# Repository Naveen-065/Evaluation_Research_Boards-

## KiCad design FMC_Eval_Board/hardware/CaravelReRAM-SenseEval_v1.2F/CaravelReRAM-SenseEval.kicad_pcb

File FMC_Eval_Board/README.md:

# FMC Evaluation Board — SenseEval v1.2F / KC705

System snapshot dated **20 October 2026**. The active implementation is
[`output/kc705_cell_control`](output/kc705_cell_control). It adapts the evaluation
research board's scan-debug, Wishbone, and GUI logic to the SenseEval FMC PCB.

This folder contains all 20 saved FPGA bitstreams from the source workspace,
their available probes/checkpoints, controller and firmware sources, PCB design
files, simulations, measurements, test programs, and raw run records.
**Use the current image identified below for this assembled PCB.** Older images
are retained for traceability and include superseded pin-use, supply, diagnostic,
and startup configurations. They are not interchangeable with the current image.

## System and signal flow

```text
Browser at 127.0.0.1:8771
  -> local Python HTTP API
  -> SSH through Ubuntu VM
  -> Windows Vivado / JTAG
  -> KC705 FPGA, FMC J2
       -> Si5351A clock configuration via FMC management I2C
       -> DAC81416 SPI: supplies, biases, SET/RESET/read rails
       -> ADS5282 control and 10-MSPS LVDS acquisition
       -> Caravel scan control or Wishbone firmware command transport

Caravel supply/current path -> 56-ohm shunt -> preamplifier
  -> ADS5282 -> FPGA accumulation/trace -> GUI/API measurements

Ubuntu VM -> PCB FT232H -> Caravel housekeeping / SPI flash
```

The GUI follows the reference ScanDisk Monitor layout: cell map, operation
controls, API return log, and one logarithmic Read Trace with pulse-voltage bars.
Conductance shown in the GUI is an **estimate**, not a calibrated cell resistance.

## Contents

| Location | Purpose |
|---|---|
| `output/kc705_cell_control/build/` | Current `.bit`, matching `.ltx`, routed `.dcp`, timing/DRC and I/O audit |
| `output/kc705_cell_control/*.v`, `*.xdc` | Current RTL and exact electrical constraints |
| `output/kc705_cell_control/control.tcl`, `scan_ramp.tcl` | Runtime operations and bounded scan ramp |
| `output/kc705_cell_control/initialize.tcl` | Explicit FPGA, clock, DAC and ADC initialization |
| `output/kc705_cell_control/gui/` | Browser UI, API, SSH startup retry implementation |
| `output/kc705_cell_control/firmware/` | Caravel C source, binary, ELF, FT232H tools and firmware SDK |
| `output/kc705_cell_control/ip/` | Four Xilinx IP configurations retrieved from the build PC |
| `output/kc705_cell_control/tests/` | Model, GUI, RTL, ramp, protocol and transport tests |
| `output/kc705_cell_control/runs/` | Per-job parameters, decoded results, raw logs and traces |
| `output/kc705_cell_control/evidence/` | Deployment records, validation reports and screenshots |
| Other `output/` folders and `build_before_*`, `build_no_trace` | Historical bring-up, earlier images and diagnostic work |
| `hardware/` | Original schematic PDF/archive and editable KiCad board, schematic and libraries |
| `source_snapshot.json` | Source-to-copy inventory and original SHA-256 values |
| `package_state.json` | Bench/API state observed during packaging and dependency provenance |
| `SHA256SUMS`, `verify_package.py` | Final package integrity verification |

Historical readmes/logs describe the state when they were written. This README
describes the current controller; notably, scan SET/RESET now use ramps, WB holds
both SE and TM low, and the GUI has one reference-style Read Trace.

## Current deployment artifacts

All paths in this table are relative to `output/kc705_cell_control/`.

| Artifact | SHA-256 |
|---|---|
| `build/kc705_adc_capture.bit` | `fe31f0249b7081b4f6a00a721002317d618b0294cad9c5306f62853f5e34427c` |
| `build/kc705_adc_capture.ltx` | `6f800d28394e1f524304c3b59190f6ef819020bd2ff781928890fca4f9248e96` |
| `firmware/gui_wb_mode.bin` | `e7ad11e318b346edaae2fd0ff30736433fb27ef3bc5c39118ab4f1fc0a4107ef` |

FPGA: **XC7K325T-FFG900-2**, KC705. Build environment: Vivado **2026.1**.
The recorded image passed setup timing (+0.360 ns), hold timing (+0.059 ns),
and the critical DRC check. The 41 exported port-property records match the
audited baseline. Use the `.ltx` belonging to this `.bit`.

The FPGA image is loaded through JTAG into volatile configuration. A power cycle
requires checking/reinitializing the FPGA and peripheral state; this package
does not install an FPGA configuration-flash boot image.

## PCB wiring and fixed electrical settings

* **FMC VADJ is 1.8 V**, as measured on this KC705 after power cycling.
  Keep the supplied XDC pin mappings, I/O standards, drive, slew, pulls and
  termination unchanged. Runtime initialization does not issue VADJ/PMBus writes.
* FMC management I2C is a separate **3.3-V** bus at KC705 J2 **C30/C31**.
  It is not made 1.8 V by setting VADJ. The board was reworked by removing
  **R53, R54 and U18**, bridging **R53-2 to R58-2** and **R54-2 to R57-2**.
  Preserve this tested wiring; consult the schematic and rework evidence before
  using a differently assembled board.
* **NT22 connects DAC14 to VDDA1, target 3.0 V; NT12 is absent.**
  **DAC15 supplies VCCD2 at 1.8 V.** Runtime DAC commands cannot modify these
  protected supply channels or the reference/range configuration.
* R9, R10 and R11 are all **56 ohms** in the tested assembly. Earlier
  documents/simulations also contain previous shunt values.
* DAC internal-reference startup is included. U1 SDO is not connected:
  FPGA completion proves command transmission, not DAC register readback.
  Verify actual supply/bias voltages with a meter after assembly changes.
* ADC operation is 10 MSPS, offset binary, LSB first, with nominal internal
  94-ohm LVDS termination. Return clocks are checked at 10 MHz and 60 MHz.
* Caravel scan operation uses a 2-MHz Si5351 clock; WB uses 10 MHz.
  Each normal job restores scan read rails and holds Caravel CPU reset.

| ADC channel | Shunt / path | Preamplifier | Differential output pads |
|---|---|---|---|
| ADC1 | R9 / READ | U10 | R37 / R38 |
| ADC2 | R11 / RESET | U13 | R46 / R47 |
| ADC3 | R10 / SET | U11 | R39 / R40 |

Scan-debug cell reads principally use **DAC2/DAC3 and ADC3/R10** on this PCB.
Do not assume that the reference board's DAC channel numbers transfer directly.
Nominal preamplifier gain is 7; independent calibration remains pending.

Scan idle targets: DAC0=0.5 V, DAC1=2.5 V, DAC2=0.5 V, DAC3=2.5 V,
DAC5=2.3 V; DAC9/IREF=0.9 V, DAC10/VCOMP=0.9 V,
DAC11/BIAS_COMP2=0.6 V, DAC12/VBIAS=1.6 V, DAC13/DC_BIAS=1.0 V.
DAC4/6/7/8 are off (mask `0x01D0`).

WB uses DAC3 off, DAC4=0.5 V, DAC5=2.5 V, IREF=1.0 V and DC_BIAS=1.5 V;
other listed biases stay unchanged. Its power mask is `0x01CC`, disabling
physical DAC2/VCC_SET. Both SE and TM are actively low in WB; floating TXS0108E
inputs can otherwise select the wrong mode. Reset remains open-drain.

## Modes and ramp behavior

Scan GUI/API modes: `read`, `set`, `reset`, `cycle`, `column` (32 rows at one
column), and `array` (32 × 32). WB modes: `wb_read`, `wb_set`, `wb_reset`,
and `wb_cycle`. Do not infer additional WB array/column support from old scripts.
The approved programming test cells were **scan r0/c0** and **WB r0/c31**.

Scan SET/RESET use the reference ramp/read/confirm logic, with these PCB limits:

| Setting | SET | RESET |
|---|---|---|
| VCC sweep | 2.3, 2.4, 2.5 V | 2.3, 2.7, 3.0 V |
| WL sweep | 32 steps, 0.44–2.37 V | 32 steps, 0.94–2.88 V |
| Confirmation threshold | Current ≥35 µA | Current ≤5 µA |
| Consecutive confirmation reads | 10 | 10 |

GUI voltage fields are sweep ceilings. **Neither ramp may exceed 3.0 V.**
The DAC encoder also caps the output code at 39321 (ideal 2.999954 V), avoiding
rounding above the cap. This is a command limit, not an independent measurement
of analog overshoot or DAC accuracy.

Each step reads first, skips programming if the target is already confirmed,
otherwise applies one pulse, restores read rails (VCC=0.5 V, WL=2.5 V), reads
again, and confirms any threshold crossing. Default pulse length is 1.2 ms
(`hold=2400` at the 2-MHz scan clock). Invalid/clipped ADC feedback or Stop
terminates the sequence. Exhausting RESET without meeting its target stops
further requested cycles; completion does not imply a successful resistance change.

WB uses the Caravel firmware's native transaction sequence, including the
repeated program-packet workaround without an intervening reset. It does not
use the scan ADC-feedback ramp. Fifteen tagged/checksummed UART frames and
command echo are checked; raw TDC results remain uncalibrated.

## Running the system

The copied configuration records these existing bench addresses and paths:

| Component | Existing configuration |
|---|---|
| GUI host | This Windows PC; loopback port 8771 |
| Ubuntu VM / SSH jump | `ubuntu-24-04@100.98.132.51` |
| FPGA Windows PC through VM | `fpga@10.0.2.2`, host-key alias `100.86.99.88` |
| Remote controller folder | `C:/Users/fpga.DESKTOP-CVDV1JP/kc705_cell_control` |
| Vivado executable | `C:/AMDDesignTools2/2026.1/Vivado/bin/vivado.bat` |
| JTAG target | `localhost:3121/xilinx_tcf/Xilinx/00001f14c98801` |

Existing SSH keys/known-host identities are required; credentials are not part
of the package. Configure a different bench in `gui/server.py`, `bench.py` and
`i2c_host.tcl`. Merely copying this folder does not redeploy remote Tcl files.

1. Verify board wiring, power and the stated rails. Connect JTAG to the FPGA
   Windows PC and pass the PCB FT232H through to Ubuntu when flashing is needed.
2. Copy the current controller folder, including `build/`, `control.tcl`,
   `scan_ramp.tcl`, other Tcl helpers, and `evidence/`, to the configured remote
   controller directory. Do not deploy a historical sibling directory.
3. After power-up or when explicit reinitialization is needed, from the current
   controller directory run `python bench.py initialize`. This programs the
   FPGA, initializes Si5351/DAC/ADC, checks clocks, and leaves the CPU held.
   It does not flash Caravel firmware.
4. If Caravel firmware is missing, use Ubuntu's existing `caravel_venv` with
   PyFTDI/PyUSB, the packaged `firmware/` files and
   `python caravel_vm.py --flash gui_wb_mode.bin --hold-after`.
   Run this on Ubuntu with the PCB FT232H attached, while the bench is idle.
5. Start one GUI server from `output/kc705_cell_control`:

   ```powershell
   python gui/server.py --port 8771
   ```

   Open `http://127.0.0.1:8771/`, use **Check bench**, then a single **Read**.
   Dry run previews a request without hardware access; clear it to execute.
   Use Stop for a controlled abort and wait for the cleanup result.

Do not run two controller servers against the same hardware. The existing
server may still be running from the original workspace; close it before
starting the packaged copy. Export links provide averaged results and the
latest decimated raw trace.

## API, trace interpretation and SSH fix status

`POST /api/run` accepts the mode, row, col, four voltage ceilings, hold, cycles
and dry_run. `GET /api/status` reports current job and recorded measurements.
`POST /api/cancel {}` requests cleanup. CSV endpoints are `/api/export.csv`
and `/api/trace.csv`; the new backend also exposes `/api/run-log/<job-id>`.

Example scan ramp cycle, which changes cell state if `dry_run` is false:

```json
{"mode":"cycle","row":0,"col":0,"set_v":2.5,"set_wl":2.37,
 "reset_v":3.0,"reset_wl":2.88,"hold":2400,"cycles":1,"dry_run":true}
```

Current is calculated as
`(active_code - idle_code) / 2048 / (7 × 56)` amperes.
The GUI's estimated conductance is this current divided by the commanded
0.5-V read supply. Pulse bars show actual ramp steps. Typical 1.2-ms captures
have about 134 decimated points at 10-µs spacing; this is not a continuous
10-MSPS oscilloscope export.

The packaged **`ssh-startup-retry-v1` API fix passed 11 fault-injection tests**.
It permits three 30-second SSH connection attempts with 2/4-second backoff
only when OpenSSH diagnostics prove failure before remote execution.
It never replays a programming command after an ambiguous disconnect.
Unconfirmed cleanup blocks further hardware operations until recovery.

**At packaging time the original live API still reported no `api_revision`:**
its restart had been blocked, so the backend fix had not been activated there.
A newly started packaged server loads the fix. Confirm `/api/status` contains
`"api_revision":"ssh-startup-retry-v1"`. Network outages can still cause a clear
failure after retries; this fix cannot guarantee permanent connectivity.
`restart_gui.ps1` is an idle-checked manual helper for an existing local server.

## Validation and remaining limitations

* Scan read, SET, RESET, cycle, column and array operations have recorded tests.
  Earlier SET/RESET coverage used fixed pulses; newer cycle records exercise ramps.
* All four WB GUI modes returned valid nonzero selected-column TDC data on the
  corrected firmware/SE/TM/power-mask path. A physical high-resistance RESET
  state and fully calibrated WB conductance have not been demonstrated.
* Ramp job `80047979cb4b4d0b9c400f1271ba7b55`: SET was already above threshold
  (10 confirmation reads, no SET pulses); RESET exhausted 96 steps and ended
  near 16.725 µA, above the ≤5-µA target.
* Later GUI cycle `01bcf263918447aebc3f995c03fd0ed5` completed with 14 SET pulses,
  SET confirmed at 37.322 µA, and 96 RESET pulses ending at 14.939 µA.
  RESET again did not reach its target. The raw run log confirms cleanup.
* Earlier loose shunt connections and a saturated ADC2 analog path were found
  during bring-up. Current calibration and independent analog verification
  remain necessary after any wiring/shunt changes.
* A prior change in r0/c0 current across WB tests was not sufficient to prove
  exclusive physical WB cell-address isolation.
* The current stored bitstream is hardware tested. Rebuilding it from the
  newly collected IP/configuration package has not been hardware validated.

## Integrity, rebuilding and offline tests

From this folder, `python verify_package.py` checks every file in `SHA256SUMS`.
`source_snapshot.json` records the original copied files; the final checksum
manifest additionally covers collected dependencies and packaging documents.

Vivado build scripts retain their original workstation paths for provenance.
`output/kc705_cell_control/build_portable.tcl` uses the packaged IP definitions
and writes a separate `build_portable/` output. It does not overwrite the tested
`build/` image or program hardware. Build with Vivado 2026.1:

```text
vivado -mode batch -source build_portable.tcl
```

Firmware SDK sources were collected from the Ubuntu bench's `caravel_board`
checkout, commit `2812cfd3896e2b1004b5f4559e0601c90cd18f55`.
Use the included firmware Makefile with a RISC-V bare-metal GCC toolchain;
the existing ELF reports GCC 14.2.0. Rebuild outputs go under `rebuilt/`
so the deployed binary remains intact. During packaging, this Makefile and
the included SDK rebuilt the firmware on Ubuntu with a **byte-identical binary**
to the deployed image. See `evidence/package_firmware_build.json` and its log.
No hardware programming was performed for this verification.

From `output/kc705_cell_control`, offline checks include:

```text
python tests/test_model.py
python tests/test_ssh_transport.py
node tests/test_reference_gui.mjs
tclsh tests/test_scan_ramp.tcl
```

These tests do not access the bench. `tests/api_bench.py`, by contrast, submits
real hardware jobs; SET/RESET/cycle modes change cell state.

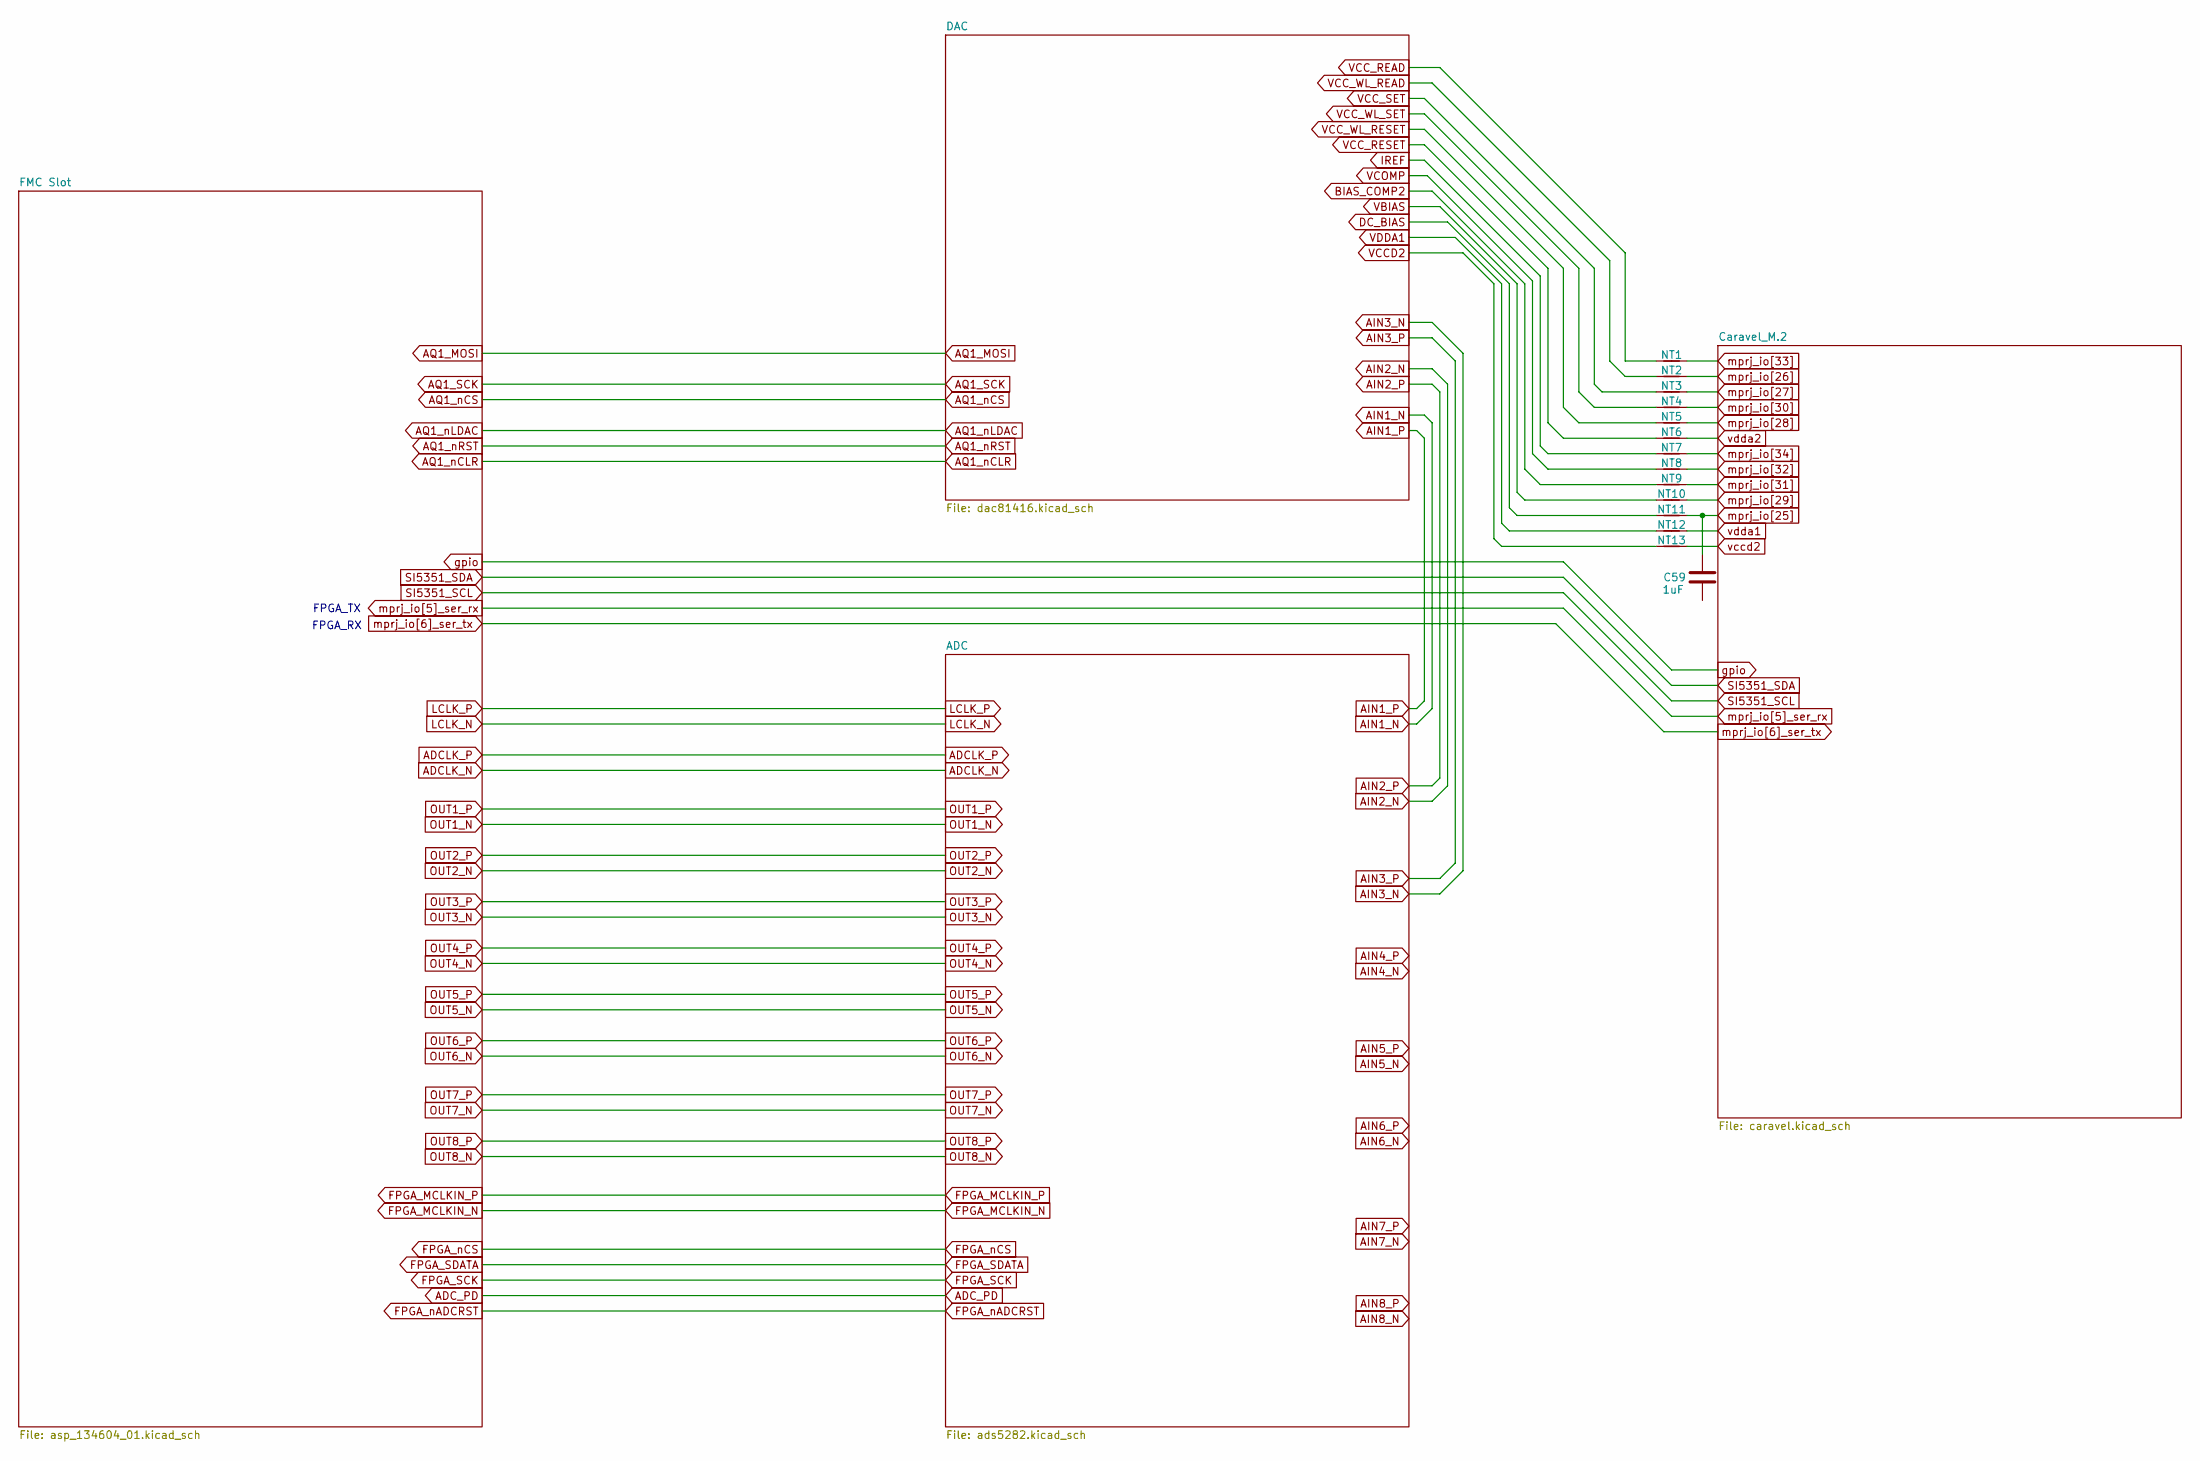
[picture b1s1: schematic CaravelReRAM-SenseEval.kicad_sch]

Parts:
C59: 1uF; C_0805_2012Metric; Part # 885012207103
NT1, NT2, NT3, NT4, NT5, NT6, NT7, NT8, NT9, NT10, NT11, NT12, NT13: NetTie_2; R_0603_1608Metric

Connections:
BIAS_COMP2: NT9.1; also elsewhere on the board
DC_BIAS: NT11.1; also elsewhere on the board
GND: C59.2; also elsewhere on the board
IREF: NT7.1; also elsewhere on the board
VBIAS: NT10.1; also elsewhere on the board
VCCD2: NT13.1; also elsewhere on the board
VCC_READ: NT1.1; also elsewhere on the board
VCC_RESET: NT6.1; also elsewhere on the board
VCC_SET: NT3.1; also elsewhere on the board
VCC_WL_READ: NT2.1; also elsewhere on the board
VCC_WL_RESET: NT5.1; also elsewhere on the board
VCC_WL_SET: NT4.1; also elsewhere on the board
VCOMP: NT8.1; also elsewhere on the board
mprj_io[25]: C59.1, NT11.2; also elsewhere on the board
mprj_io[26]: NT2.2; also elsewhere on the board
mprj_io[27]: NT3.2; also elsewhere on the board
mprj_io[28]: NT5.2; also elsewhere on the board
mprj_io[29]: NT10.2; also elsewhere on the board
mprj_io[30]: NT4.2; also elsewhere on the board
mprj_io[31]: NT9.2; also elsewhere on the board
mprj_io[32]: NT8.2; also elsewhere on the board
mprj_io[33]: NT1.2; also elsewhere on the board
mprj_io[34]: NT7.2; also elsewhere on the board
vccd2: NT13.2; also elsewhere on the board
vdda1: NT12.2; also elsewhere on the board
vdda2: NT6.2; also elsewhere on the board

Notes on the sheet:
FPGA_TX
FPGA_RX

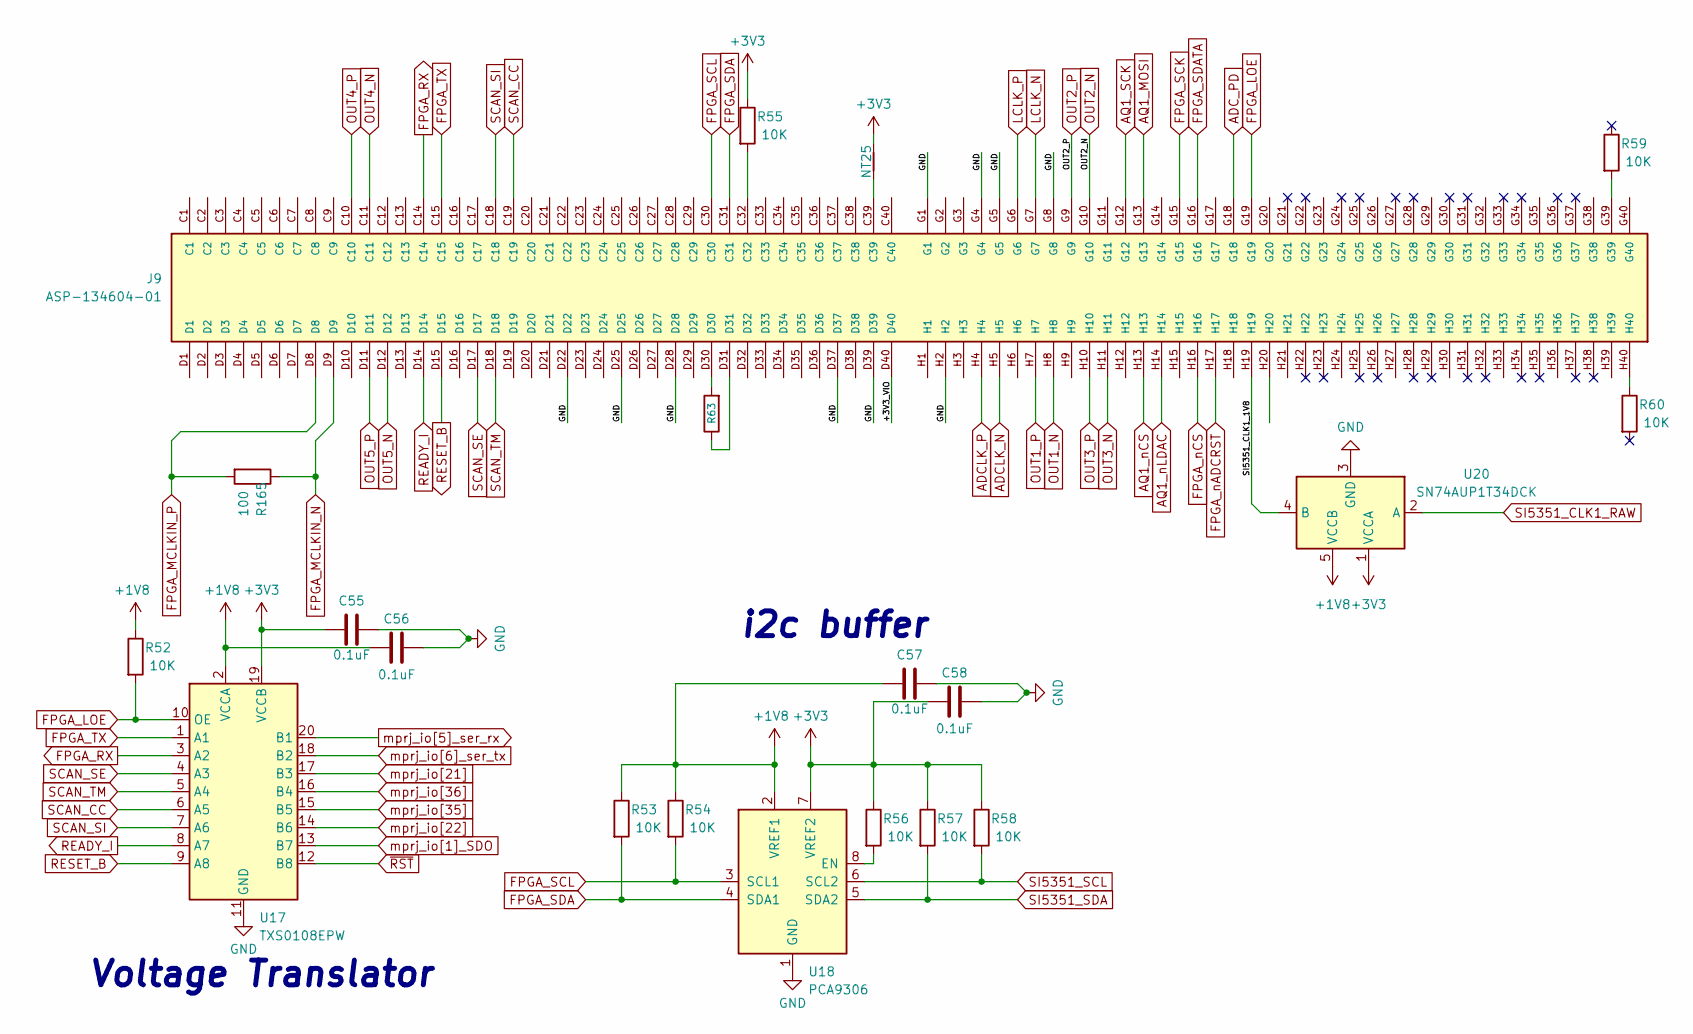
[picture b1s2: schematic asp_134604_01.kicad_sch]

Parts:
C55, C56, C57, C58: 0.1uF; C_0805_2012Metric; Part # C0805C104K5RAC7411
J9: ASP-134604-01; Samtec_FMC_ASP-134604-01_4x40_Vertical; PARTREV S
NT25: NetTie_2; R_0603_1608Metric
R52, R53, R54, R55, R56, R57, R58, R59, R60: 10K; R_0805_2012Metric; Part # RC0805FR-0710KL
R63: ERJ-8GEY0R00V; R_1206_3216Metric_Pad1.30x1.75mm_HandSolder
R165: 100; R_0402_1005Metric; Part # RC0805FR-0710KL
U17: TXS0108EPW; TSSOP-20_4.4x6.5mm_P0.65mm
U18: PCA9306; SSOP-8_2.95x2.8mm_P0.65mm
U20: SN74AUP1T34DCK; SOT-353_SC-70-5

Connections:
3V3FMC: J9.C39, NT25.1
/Caravel_M.2/ACBUS1: U17.12 (B8); also elsewhere on the board
/Caravel_M.2/SI5351_CLK1_RAW: U20.2 (A); also elsewhere on the board
/Caravel_M.2/USB_SI: U17.13 (B7); also elsewhere on the board
/FMC Slot/+3V3_VIO: J9.D40
ADCLK_N: J9.H5; also elsewhere on the board
ADCLK_P: J9.H4; also elsewhere on the board
ADC_PD: J9.G18; also elsewhere on the board
AQ1_MOSI: J9.G13; also elsewhere on the board
AQ1_SCK: J9.G12; also elsewhere on the board
AQ1_nCS: J9.H13; also elsewhere on the board
AQ1_nLDAC: J9.H14; also elsewhere on the board
AQ1_nRST: J9.H20; also elsewhere on the board
FPGA_LOE: J9.G19, R52.2, U17.10 (OE)
FPGA_RX: J9.C14, U17.3 (A2)
FPGA_SCK: J9.G15; also elsewhere on the board
FPGA_SCL: J9.C30, R54.2, U18.3 (SCL1)
FPGA_SDA: J9.C31, R53.2, U18.4 (SDA1)
FPGA_SDATA: J9.G16; also elsewhere on the board
FPGA_TX: J9.C15, U17.1 (A1)
FPGA_nADCRST: J9.H17; also elsewhere on the board
FPGA_nCS: J9.H16; also elsewhere on the board
GND: C55.1, C56.1, C57.1, C58.1, J9.C34, J9.D22, J9.D25, J9.D28, J9.D37, J9.D39, J9.G1, J9.G4, J9.G5, J9.G8, J9.H2, U17.11 (GND), U18.1 (GND), U20.3 (GND); also elsewhere on the board
LCLK_N: J9.G7; also elsewhere on the board
LCLK_P: J9.G6; also elsewhere on the board
unnamed: J9.C32, R55.2
unnamed: J9.G39, R59.2
unnamed: J9.H40, R60.1
unnamed: R56.2, U18.8 (EN)
OUT1_N: J9.H8; also elsewhere on the board
OUT1_P: J9.H7; also elsewhere on the board
OUT2_N: J9.G10; also elsewhere on the board
OUT2_P: J9.G9; also elsewhere on the board
OUT3_N: J9.H11; also elsewhere on the board
OUT3_P: J9.H10; also elsewhere on the board
OUT4_N: J9.C11; also elsewhere on the board
OUT4_P: J9.C10; also elsewhere on the board
OUT5_N: J9.D12; also elsewhere on the board
OUT5_P: J9.D11; also elsewhere on the board
READY_I: J9.D14, U17.8 (A7)
RESET_B: J9.D15, U17.9 (A8)
SCAN_CC: J9.C19, U17.6 (A5)
SCAN_SE: J9.D17, U17.4 (A3)
SCAN_SI: J9.C18, U17.7 (A6)
SCAN_TM: J9.D18, U17.5 (A4)
SI5351_CLK1_1V8: J9.H19, U20.4 (Y)
SI5351_SCL: R58.2, U18.6 (SCL2); also elsewhere on the board
SI5351_SDA: R57.2, U18.5 (SDA2); also elsewhere on the board
mprj_io[21]: U17.17 (B3); also elsewhere on the board
mprj_io[22]: U17.14 (B6); also elsewhere on the board
mprj_io[35]: U17.15 (B5); also elsewhere on the board
mprj_io[36]: U17.16 (B4); also elsewhere on the board

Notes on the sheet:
i2c buffer
Voltage Translator

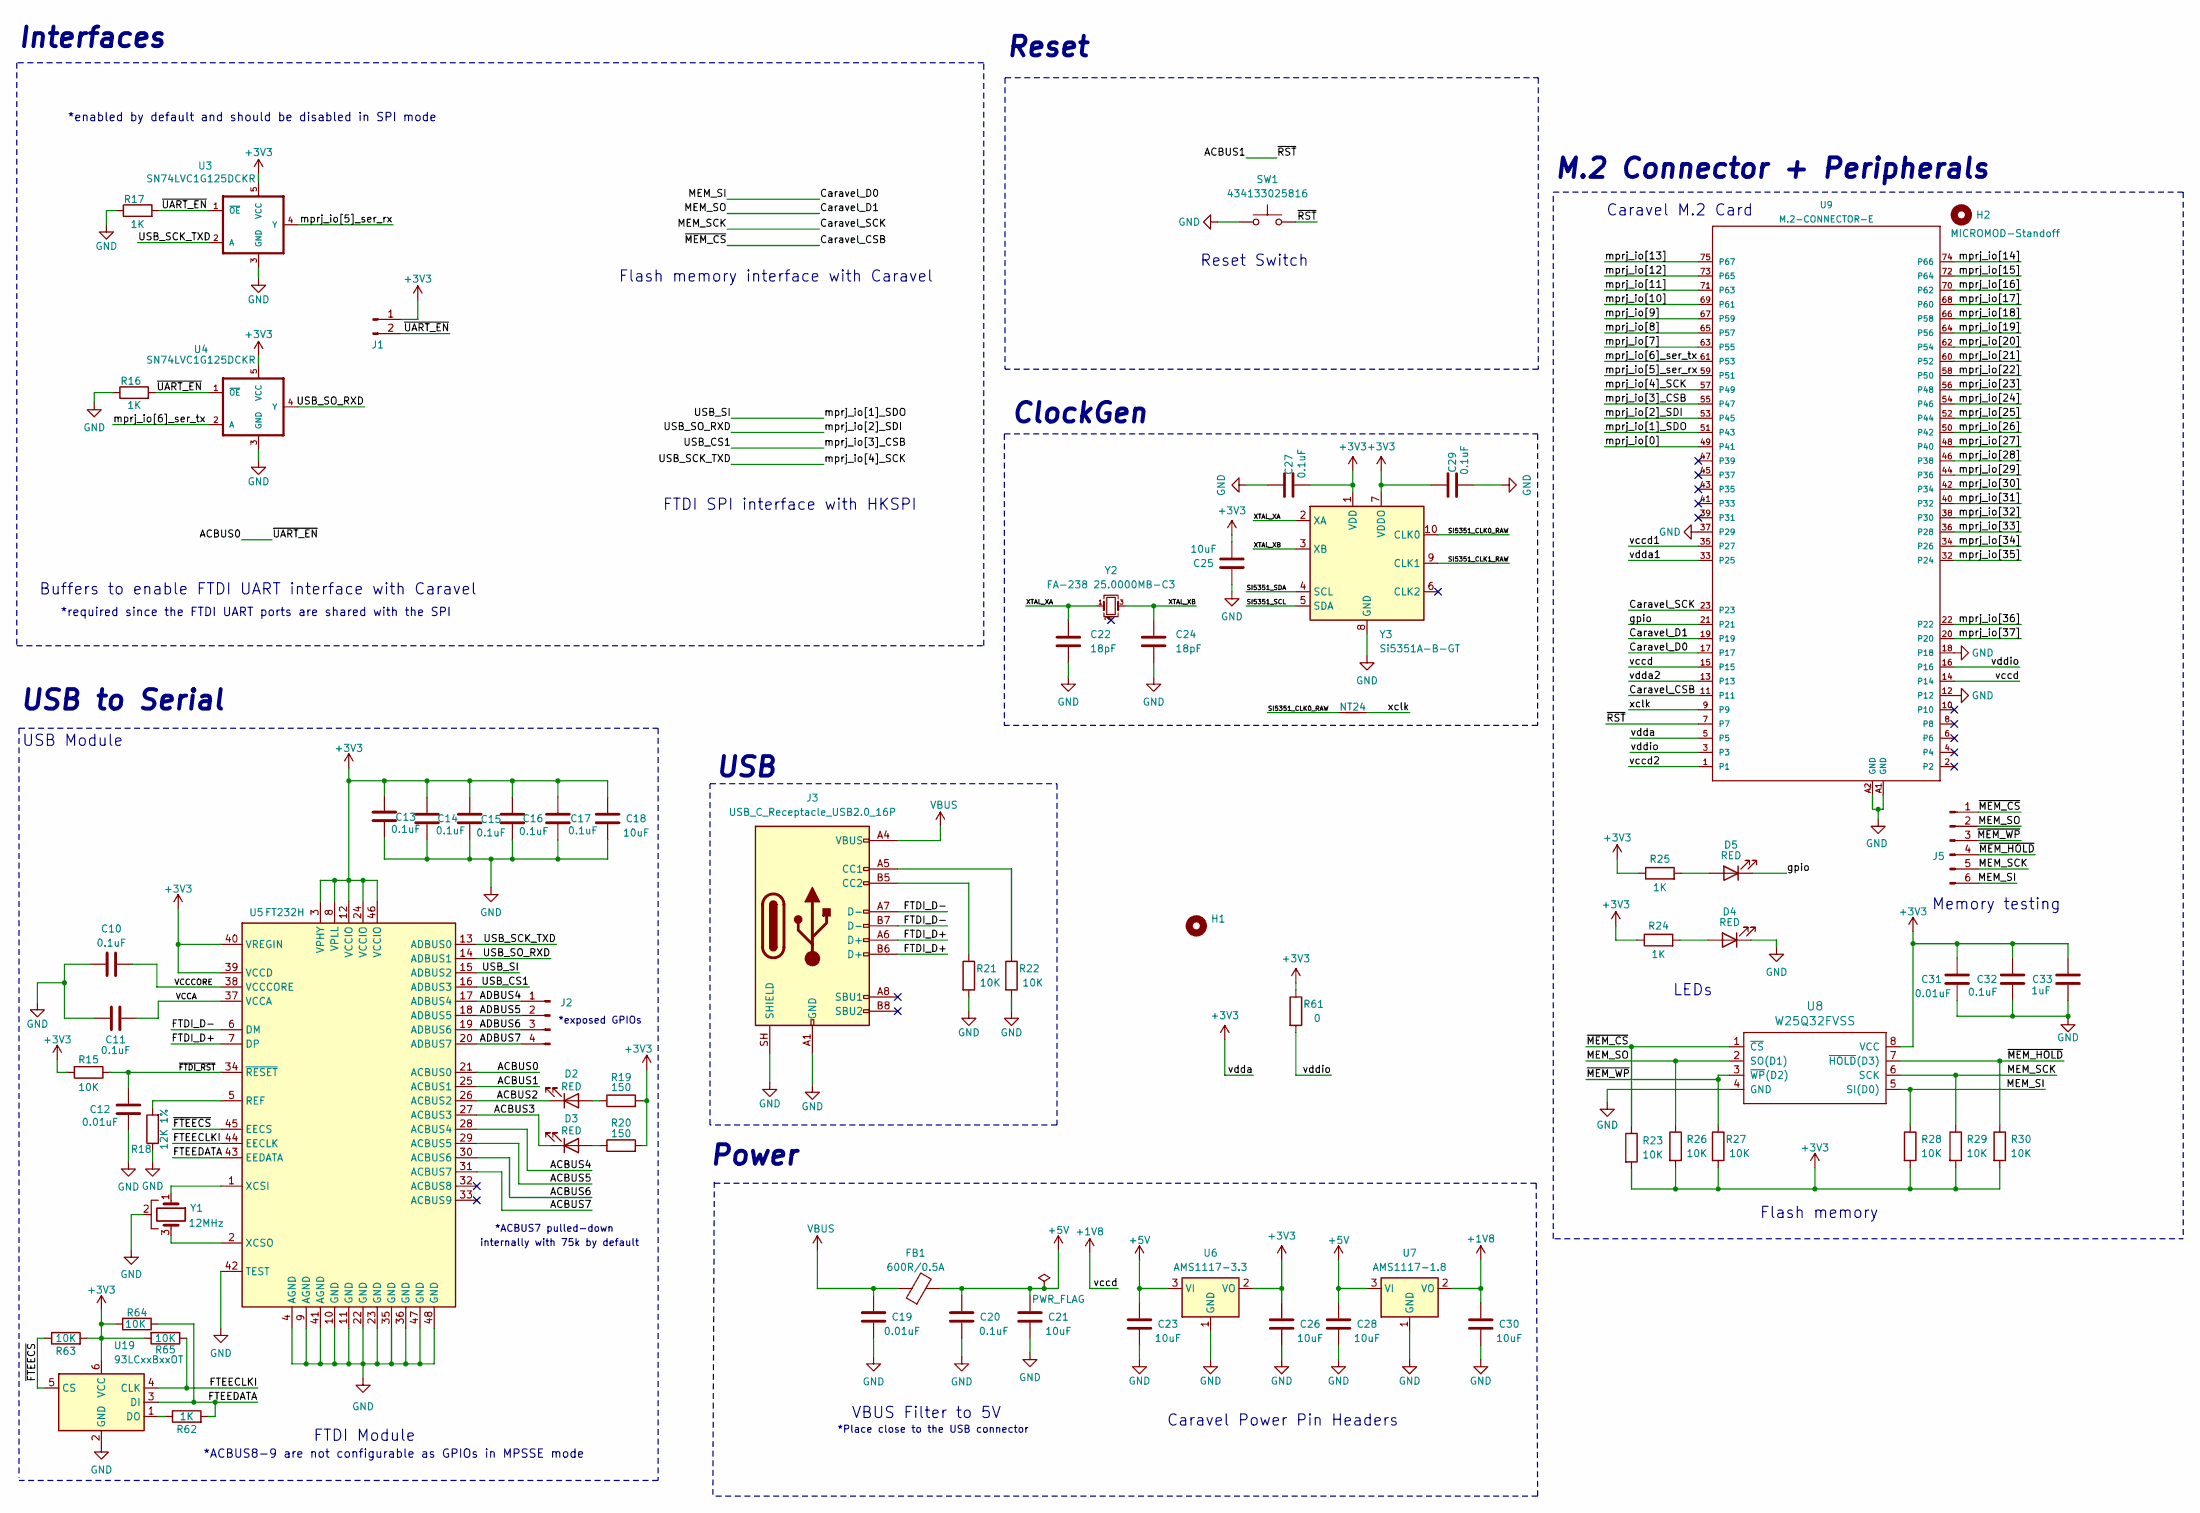
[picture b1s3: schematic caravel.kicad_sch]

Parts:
C10, C11, C13, C14, C15, C16, C17, C20, C27, C29, C32: 0.1uF; C_0805_2012Metric; Part # C0805C104K5RAC7411
C12, C19, C31: 0.01uF; C_0805_2012Metric; Part # C0805C103K5RAC7411
C18, C21, C23, C25, C26, C28, C30: 10uF; C_0805_2012Metric; Part # CL21B106KAYQNNE
C22, C24: 18pF; C_0805_2012Metric
C33: 1uF; C_0805_2012Metric; Part # 885012207103
D2, D3, D4, D5: RED; LED_1206_3216Metric; Part # LTST-C230KRKT
FB1: 600R/0.5A; L_0805_2012Metric; Part # 7427920415
H1: (no value)
H2: MICROMOD-Standoff; MicroMod-Standoff
J1: Conn_01x02_Pin; PinHeader_1x02_P2.54mm_Vertical
J2: Conn_01x04_Pin; PinHeader_1x04_P2.54mm_Vertical
J3: USB_C_Receptacle_USB2.0_16P; USB_C_Receptacle_GCT_USB4085
J5: Conn_01x06_Pin; PinHeader_1x06_P2.54mm_Vertical
NT24: NetTie_2; R_0603_1608Metric
R15, R21, R22, R23, R26, R27, R28, R29, R30, R63, R64, R65: 10K; R_0805_2012Metric; Part # RC0805FR-0710KL
R16, R17, R24, R25, R62: 1K; R_0805_2012Metric; Part # RC0805FR-071KL
R18: 12K 1%; R_0805_2012Metric; Part # RMCF0805FT12K0
R19, R20: 150; R_0805_2012Metric; Part # RNCP0805FTD150R
R61: 0; R_0805_2012Metric; Part # RMCF0805ZT0R00
SW1: 434133025816; SW_Push_1P1T_NO_Vertical_Wuerth_434133025816
U3, U4: SN74LVC1G125DCKR; Texas_R-PDSO-G5_DCK-5; Part # SN74LVC1G125DCKR
U5: FT232H; QFN-48-1EP_8x8mm_P0.5mm_EP6.2x6.2mm; Part # FT232H
U6: AMS1117-3.3; SOT-223-3_TabPin2
U7: AMS1117-1.8; SOT-223-3_TabPin2
U8: W25Q32FVSS; SOIC-8_5.3x5.3mm_P1.27mm; Part # W25Q32JVSSIQ
U9: M.2-CONNECTOR-E
U19: 93LCxxBxxOT; SOT-23-6_Handsoldering
Y1: 12MHz; Resonator_SMD_Murata_CSTxExxV-3Pin_3.0x1.1mm; Part # CSTNE12M0GH5L000R0
Y2: FA-238 25.0000MB-C3; Crystal_SMD_3225-4Pin_3.2x2.5mm_HandSoldering
Y3: Si5351A-B-GT; MSOP-10_3x3mm_P0.5mm

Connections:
+5V: C20.2, C21.2, C23.1, C28.1, FB1.2, U6.3 (VI), U7.3 (VI); also elsewhere on the board
/Caravel_M.2/ACBUS0: J1.2, R16.2, R17.2, U3.1 (~OE), U4.1 (~OE), U5.21 (ACBUS0)
/Caravel_M.2/ACBUS1: SW1.2, U5.25 (ACBUS1), U9.7; also elsewhere on the board
/Caravel_M.2/ACBUS2: D2.1 (K), U5.26 (ACBUS2)
/Caravel_M.2/ACBUS3: D3.1 (K), U5.27 (ACBUS3)
/Caravel_M.2/ACBUS4: U5.28 (ACBUS4)
/Caravel_M.2/ACBUS5: U5.29 (ACBUS5)
/Caravel_M.2/ACBUS6: U5.30 (ACBUS6)
/Caravel_M.2/ACBUS7: U5.31 (ACBUS7)
/Caravel_M.2/ADBUS4: J2.1, U5.17 (ADBUS4)
/Caravel_M.2/ADBUS5: J2.2, U5.18 (ADBUS5)
/Caravel_M.2/ADBUS6: J2.3, U5.19 (ADBUS6)
/Caravel_M.2/ADBUS7: J2.4, U5.20 (ADBUS7)
/Caravel_M.2/Caravel_CSB: J5.1, R23.1, U8.1 (~CS), U9.11
/Caravel_M.2/Caravel_D0: J5.6, R28.1, U8.5 (SI(D0)), U9.17
/Caravel_M.2/Caravel_D1: J5.2, R26.1, U8.2 (SO(D1)), U9.19
/Caravel_M.2/Caravel_SCK: J5.5, R29.1, U8.6 (SCK), U9.23
/Caravel_M.2/FTDI_D+: J3.A6 (D+), J3.B6 (D+), U5.7 (DP)
/Caravel_M.2/FTDI_D-: J3.A7 (D-), J3.B7 (D-), U5.6 (DM)
/Caravel_M.2/SI5351_CLK0_RAW: NT24.1, Y3.10 (CLK0)
/Caravel_M.2/SI5351_CLK1_RAW: Y3.9 (CLK1); also elsewhere on the board
/Caravel_M.2/USB_CS1: U5.16 (ADBUS3), U9.55 (P47)
/Caravel_M.2/USB_SCK_TXD: U3.2 (A), U5.13 (ADBUS0), U9.57 (P49)
/Caravel_M.2/USB_SI: U5.15 (ADBUS2), U9.51 (P43); also elsewhere on the board
/Caravel_M.2/USB_SO_RXD: U4.4 (Y), U5.14 (ADBUS1), U9.53 (P45)
/Caravel_M.2/VCCA: C11.2, U5.37 (VCCA)
/Caravel_M.2/VCCCORE: C10.2, U5.38 (VCCCORE)
/Caravel_M.2/XTAL_XA: C22.1, Y2.1, Y3.2 (XA)
/Caravel_M.2/XTAL_XB: C24.1, Y2.3, Y3.3 (XB)
/Caravel_M.2/gpio: D5.1 (K), U9.21
/Caravel_M.2/mprj_io[0]: U9.49 (P41)
/Caravel_M.2/mprj_io[7]: U9.63 (P55)
/Caravel_M.2/mprj_io[8]: U9.65 (P57)
/Caravel_M.2/mprj_io[9]: U9.67 (P59)
/Caravel_M.2/mprj_io[10]: U9.69 (P61)
/Caravel_M.2/mprj_io[11]: U9.71 (P63)
/Caravel_M.2/mprj_io[12]: U9.73 (P65)
/Caravel_M.2/mprj_io[13]: U9.75 (P67)
/Caravel_M.2/mprj_io[14]: U9.74 (P66)
/Caravel_M.2/mprj_io[15]: U9.72 (P64)
/Caravel_M.2/mprj_io[16]: U9.70 (P62)
/Caravel_M.2/mprj_io[17]: U9.68 (P60)
/Caravel_M.2/mprj_io[18]: U9.66 (P58)
/Caravel_M.2/mprj_io[19]: U9.64 (P56)
/Caravel_M.2/mprj_io[20]: U9.62 (P54)
/Caravel_M.2/mprj_io[23]: U9.56 (P48)
/Caravel_M.2/mprj_io[24]: U9.54 (P46)
/Caravel_M.2/mprj_io[37]: U9.20
/Caravel_M.2/xclk: NT24.2, U9.9
/Caravel_M.2/~FTDI_RST: C12.2, R15.1, U5.34 (~RESET)
/Caravel_M.2/~MEM_HOLD: J5.4, R30.1, U8.7 (~HOLD(D3))
/Caravel_M.2/~MEM_WP: J5.3, R27.1, U8.3 (~WP(D2))
FTEECLKI: R65.1, U5.44 (EECLK), U19.4 (CLK)
GND: C10.1, C11.1, C12.1, C13.1, C14.1, C15.1, C16.1, C17.1, C18.2, C19.2, C20.1, C21.1, C22.2, C23.2, C24.2, C25.1, C26.2, C27.2, C28.2, C29.1, C30.2, C31.1, C32.2, C33.2, D4.1 (K), J3.A1 (GND), J3.A12 (GND), J3.B1 (GND), J3.B12 (GND), J3.SH (SHIELD), R16.1, R17.1, R18.1, R21.2, R22.2, SW1.1, U3.3 (GND), U4.3 (GND), U5.4 (AGND), U5.9 (AGND), U5.10 (GND), U5.11 (GND), U5.22 (GND), U5.23 (GND), U5.35 (GND), U5.36 (GND), U5.41 (AGND), U5.42 (TEST), U5.47 (GND), U5.48 (GND), U5.49, U6.1 (GND), U7.1 (GND), U8.4 (GND), U9.12, U9.18, U9.37 (P29), U9.A1 (GND), U9.A2 (GND), U19.2 (GND), Y1.2, Y3.8 (GND); also elsewhere on the board
unnamed: D2.2 (A), R19.1
unnamed: D3.2 (A), R20.1
unnamed: D4.2 (A), R24.2
unnamed: D5.2 (A), R25.2
unnamed: J3.A5 (CC1), R22.1
unnamed: J3.B5 (CC2), R21.1
unnamed: R18.2, U5.5 (REF)
unnamed: U5.1 (XCSI), Y1.1
unnamed: U5.2 (XCSO), Y1.3
SI5351_SCL: Y3.5 (SDA); also elsewhere on the board
SI5351_SDA: Y3.4 (SCL); also elsewhere on the board
VBUS: C19.1, FB1.1, J3.A4 (VBUS), J3.A9 (VBUS), J3.B4 (VBUS), J3.B9 (VBUS)
mprj_io[21]: U9.60 (P52); also elsewhere on the board
mprj_io[22]: U9.58 (P50); also elsewhere on the board
mprj_io[25]: U9.52 (P44); also elsewhere on the board
mprj_io[26]: U9.50 (P42); also elsewhere on the board
mprj_io[27]: U9.48 (P40); also elsewhere on the board
mprj_io[28]: U9.46 (P38); also elsewhere on the board
mprj_io[29]: U9.44 (P36); also elsewhere on the board
mprj_io[30]: U9.42 (P34); also elsewhere on the board
mprj_io[31]: U9.40 (P32); also elsewhere on the board
mprj_io[32]: U9.38 (P30); also elsewhere on the board
mprj_io[33]: U9.36 (P28); also elsewhere on the board
mprj_io[34]: U9.34 (P26); also elsewhere on the board
mprj_io[35]: U9.32 (P24); also elsewhere on the board
mprj_io[36]: U9.22; also elsewhere on the board
vccd2: U9.1; also elsewhere on the board
vdda1: U9.33 (P25); also elsewhere on the board
vdda2: U9.13; also elsewhere on the board

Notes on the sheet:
Reset Switch
Buffers to enable FTDI UART interface with Caravel
FTDI SPI interface with HKSPI
ClockGen
Caravel M.2 Card
LEDs
*required since the FTDI UART ports are shared with the SPI
FTDI Module
Memory testing
USB
*enabled by default and should be disabled in SPI mode
Flash memory interface with Caravel
*ACBUS8-9 are not configurable as GPIOs in MPSSE mode
VBUS Filter to 5V
Caravel Power Pin Headers
*exposed GPIOs
USB to Serial
Flash memory
Interfaces
M.2 Connector + Peripherals
*ACBUS7 pulled-down
Reset
Power
internally with 75k by default
USB Module
*Place close to the USB connector

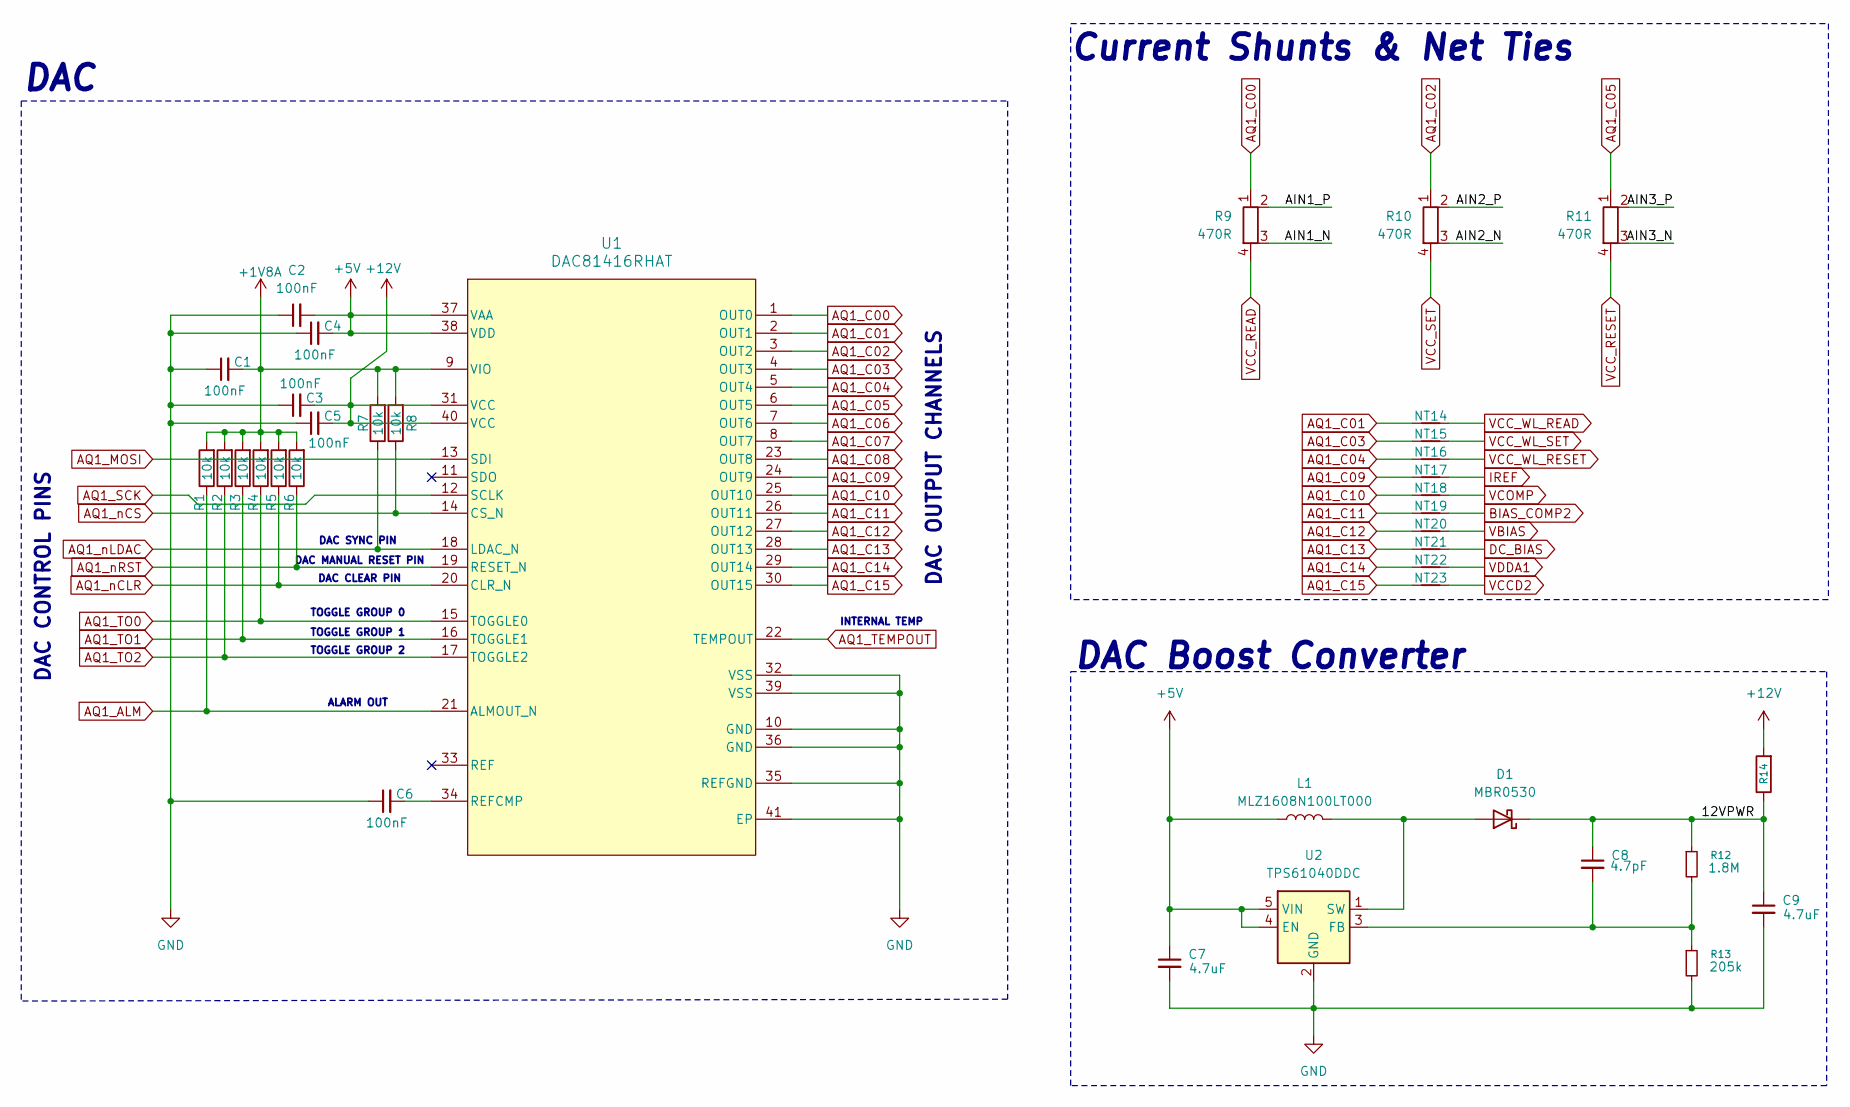
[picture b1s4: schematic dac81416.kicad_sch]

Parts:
C1, C2, C3, C4, C5, C6: 100nF; C_1206_3216Metric
C7, C9: GRM188R61E475KE11D; C_0603_1608Metric_Pad1.08x0.95mm_HandSolder
C8: CL10C4R7BB8NNNC; C_0603_1608Metric_Pad1.08x0.95mm_HandSolder
D1: MBR0530; D_SOD-123
L1: MLZ1608N100LT000; L_0603_1608Metric_Pad1.05x0.95mm_HandSolder
NT14, NT15, NT16, NT17, NT18, NT19, NT20, NT21, NT22, NT23: NetTie_2; R_0603_1608Metric
R1, R2, R3, R4, R5, R6: 10k; R_0805_2012Metric
R7, R8: 10k; R_0805_2012Metric_Pad1.20x1.40mm_HandSolder
R9, R10, R11: 470R; R_Shunt_Vishay_WSK2512_6332Metric_T1.19mm
R12: MCT06030C1804FP500; R_0603_1608Metric_Pad0.98x0.95mm_HandSolder
R13: ERA-3AEB2053V; R_0603_1608Metric_Pad0.98x0.95mm_HandSolder
R14: ERJ-8GEY0R00V; R_1206_3216Metric_Pad1.30x1.75mm_HandSolder
U1: DAC81416RHAT; Texas_RHA0040D_VQFN-40-1EP_6x6mm_P0.5mm_EP2.9x2.9mm_Thermal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
U2: TPS61040DDC; SOT-23-5

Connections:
+1V8A: C1.2, R1.2, R2.2, R3.2, R4.2, R5.2, R6.2, R7.2, R8.2, U1.9 (VIO); also elsewhere on the board
+5V: C2.2, C4.2, C7.1, L1.1, U1.37 (VAA), U1.38 (VDD), U2.4 (EN), U2.5 (VIN); also elsewhere on the board
+12V: C3.2, C5.2, R14.2, U1.31 (VCC), U1.40 (VCC); also elsewhere on the board
/DAC/12VPWR: C8.1, C9.1, D1.1 (K), R12.1, R14.1
AIN1_N: R9.3; also elsewhere on the board
AIN1_P: R9.2; also elsewhere on the board
AIN2_N: R10.3; also elsewhere on the board
AIN2_P: R10.2; also elsewhere on the board
AIN3_N: R11.3; also elsewhere on the board
AIN3_P: R11.2; also elsewhere on the board
AQ1_ALM: R1.1, U1.21 (ALMOUT_N)
AQ1_C00: R9.1, U1.1 (OUT0)
AQ1_C01: NT14.1, U1.2 (OUT1)
AQ1_C02: R10.1, U1.3 (OUT2)
AQ1_C03: NT15.1, U1.4 (OUT3)
AQ1_C04: NT16.1, U1.5 (OUT4)
AQ1_C05: R11.1, U1.6 (OUT5)
AQ1_C06: U1.7 (OUT6)
AQ1_C07: U1.8 (OUT7)
AQ1_C08: U1.23 (OUT8)
AQ1_C09: NT17.1, U1.24 (OUT9)
AQ1_C10: NT18.1, U1.25 (OUT10)
AQ1_C11: NT19.1, U1.26 (OUT11)
AQ1_C12: NT20.1, U1.27 (OUT12)
AQ1_C13: NT21.1, U1.28 (OUT13)
AQ1_C14: NT22.1, U1.29 (OUT14)
AQ1_C15: NT23.1, U1.30 (OUT15)
AQ1_MOSI: U1.13 (SDI); also elsewhere on the board
AQ1_SCK: U1.12 (SCLK); also elsewhere on the board
AQ1_TEMPOUT: U1.22 (TEMPOUT)
AQ1_TO0: R4.1, U1.15 (TOGGLE0)
AQ1_TO1: R3.1, U1.16 (TOGGLE1)
AQ1_TO2: R2.1, U1.17 (TOGGLE2)
AQ1_nCLR: R5.1, U1.20 (CLR_N)
AQ1_nCS: R8.1, U1.14 (CS_N); also elsewhere on the board
AQ1_nLDAC: R7.1, U1.18 (LDAC_N); also elsewhere on the board
AQ1_nRST: R6.1, U1.19 (RESET_N); also elsewhere on the board
BIAS_COMP2: NT19.2; also elsewhere on the board
DC_BIAS: NT21.2; also elsewhere on the board
GND: C1.1, C2.1, C3.1, C4.1, C5.1, C6.1, C7.2, C9.2, R13.2, U1.10 (GND), U1.32 (VSS), U1.35 (REFGND), U1.36 (GND), U1.39 (VSS), U1.41 (EP), U2.2 (GND); also elsewhere on the board
IREF: NT17.2; also elsewhere on the board
unnamed: D1.2 (A), L1.2, U2.1 (SW)
unnamed: C6.2, U1.34 (REFCMP)
unnamed: C8.2, R12.2, R13.1, U2.3 (FB)
VBIAS: NT20.2; also elsewhere on the board
VCCD2: NT23.2; also elsewhere on the board
VCC_READ: R9.4; also elsewhere on the board
VCC_RESET: R11.4; also elsewhere on the board
VCC_SET: R10.4; also elsewhere on the board
VCC_WL_READ: NT14.2; also elsewhere on the board
VCC_WL_RESET: NT16.2; also elsewhere on the board
VCC_WL_SET: NT15.2; also elsewhere on the board
VCOMP: NT18.2; also elsewhere on the board
vdda1: NT22.2; also elsewhere on the board

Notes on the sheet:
DAC SYNC PIN
DAC Boost Converter
TOGGLE GROUP 1
Current Shunts & Net Ties
TOGGLE GROUP 0
DAC CONTROL PINS
DAC CLEAR PIN
ALARM OUT
DAC MANUAL RESET PIN
INTERNAL TEMP
DAC OUTPUT CHANNELS
TOGGLE GROUP 2
DAC
